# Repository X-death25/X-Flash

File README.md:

# X-Flash
An Open Source CPLD based Sega Megadrive/Genesis Flash Cart 

What is it ?
-----

X-flash is my Sega Megadrive developpement cartridge.
I use it for some research and do all of my hardware test.
It's based on the good old EPM240 and a 64Mb flash memory

Product Feature :
-----

    Rewritable 64 Mb Flash ROM
    192 Macrocells CPLD
    Clean 5V <> 3.3V level shifting
    7 GPIO for user
    Open Source Hardware & Software & PCB

Cartridge supported :
-----
    Classic 32Mb cartridge ( no mapper )

How to use it :
-----

Just flash the needed core into the CPLD and cartridge will works in the same way as an original.
You can reflash memory with any compatible Megadrive reader ( for exemple MD Dumper / Krikkz / Sanni cart Reader )

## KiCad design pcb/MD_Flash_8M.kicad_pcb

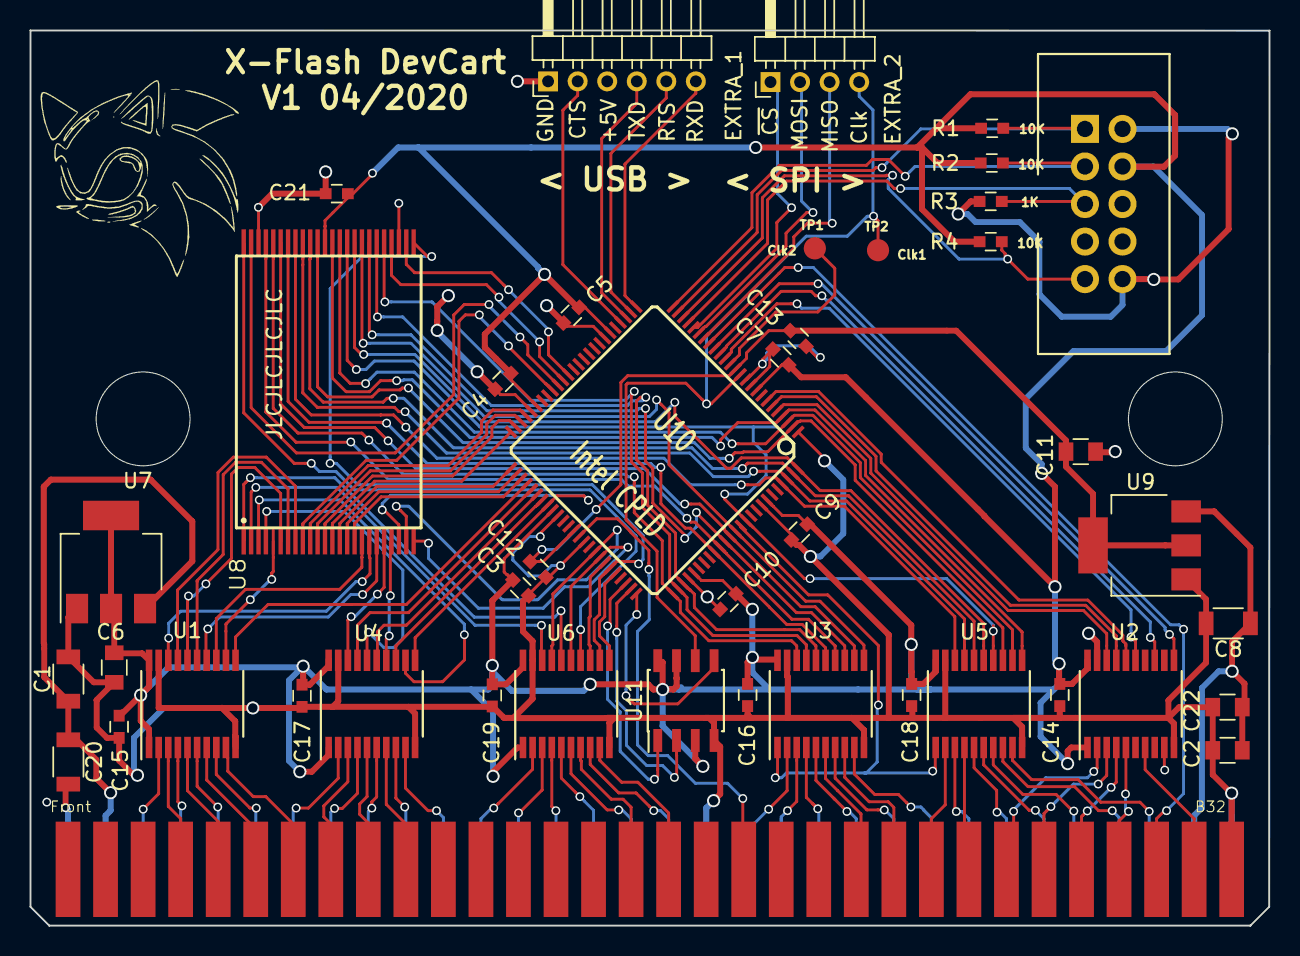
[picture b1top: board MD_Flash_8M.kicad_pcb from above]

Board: 2 copper layers, 83.8 x 60.6 mm, 41 parts (0 on the bottom side), 116 nets.

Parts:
C1, C8, C20: 1206_C; C_1206
C2, C6, C11, C22: C_0805
C3, C4, C5, C7, C9, C10, C12, C13, C14, C15, C16, C17, C18, C19, C21: 0603_CD; C_0603
EXTRA_1: Pin_Header_Angled_1x06_Pitch2.00mm
EXTRA_2: Pin_Header_Angled_1x04_Pitch2.00mm
J1: 0; AVR-JTAG-ICE
MD_Connector1: MD_Connector_H; MEGADRIVE_PCB
R1, R2, R3, R4: R_0603; C_0603
U1, U2, U3, U4, U5, U6: 74LVC245; TSSOP-20_4.4x6.5mm_Pitch0.65mm
U7, U9: SOT-223
U8: MX29LV640; S29GL064
U10: Intel CPLD; TQFP_100
U11: AT25xxx; SOIC-8_3.9x4.9mm_Pitch1.27mm

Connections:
5V1: C2.2, C8.1, C22.2, MD_Connector1.A31, U9.3
5V2: C1.1, C20.1, MD_Connector1.A2, U7.3
A1: MD_Connector1.A17, U6.8
A2: MD_Connector1.A15, U6.5
A3: MD_Connector1.A13, U6.3
A4: MD_Connector1.A11, U4.9
A5: MD_Connector1.A9, U4.6
A6: MD_Connector1.A7, U4.2
A7: MD_Connector1.A5, U1.6
A8: MD_Connector1.A3, U1.2
A9: MD_Connector1.B4, U1.3
A10: MD_Connector1.B5, U1.5
A11: MD_Connector1.A4, U1.4
A12: MD_Connector1.A6, U1.8
A13: MD_Connector1.A8, U4.4
A14: MD_Connector1.A10, U4.8
A15: MD_Connector1.A12, U6.2
A16: MD_Connector1.A14, U6.4
A17: MD_Connector1.A16, U6.6
A18: MD_Connector1.B6, U1.7
A19: MD_Connector1.B7, U1.9
A20: MD_Connector1.B8, U4.3
A21: MD_Connector1.B9, U4.5
A22: MD_Connector1.B10, U4.7
ACC: U8.14, U10.51
BUF_Dir: U3.1, U5.1, U10.89
BYTE: U8.47, U10.41
CE_SPI: U10.73, U11.1
Clk_SPI: EXTRA_2.4, U10.12, U11.6
D0: MD_Connector1.A20, U3.3
D1: MD_Connector1.A23, U3.7
D2: MD_Connector1.A26, U5.5
D3: MD_Connector1.A29, U5.8
D4: MD_Connector1.A28, U5.7
D5: MD_Connector1.A25, U5.3
D6: MD_Connector1.A22, U3.5
D7: MD_Connector1.A19, U3.2
D8: MD_Connector1.A21, U3.4
D9: MD_Connector1.A24, U3.9
D10: MD_Connector1.A27, U5.6
D11: MD_Connector1.A30, U5.9
D12: MD_Connector1.B25, U5.4
D13: MD_Connector1.B24, U5.2
D14: MD_Connector1.B23, U3.8
D15: MD_Connector1.B22, U3.6
FA19: U8.16, U10.53
FA20: U8.9, U10.42
FA21: U8.10, U10.47
FA22: U8.13, U10.50
FCE: U8.26, U10.39
FOE: U8.28, U10.40
GND: C1.2, C2.1, C3.1, C4.2, C5.2, C6.2, C7.2, C8.2, C9.2, C10.2, C11.2, C12.1, C13.1, C14.1, C15.2, C16.1, C17.1, C18.1, C19.1, C20.2, C21.1, C22.1, EXTRA_1.1, J1.2, J1.10, MD_Connector1.A1, MD_Connector1.A18, MD_Connector1.A32, MD_Connector1.B32, R3.2, U1.10, U1.19, U2.10, U3.10, U3.19, U4.10, U4.19, U5.10, U5.19, U6.10, U6.19, U7.1, U8.27, U8.46, U9.1, U10.1, U10.10, U10.11, U10.32, U10.46, U10.60, U10.65, U10.79, U10.93, U11.4
MISO: U10.74, U11.2
MOSI: U10.75, U11.5
RY-BY: U8.15, U10.52
TCK: J1.1, R1.1, U10.24
TDI: J1.9, R4.1, U10.23
TDO: J1.3, R2.1, U10.25
TMS: J1.5, R3.1, U10.22
VA1: U6.12, U8.25, U10.70
VA2: U6.15, U8.24, U10.68
VA3: U6.17, U8.23, U10.67
VA4: U4.11, U8.22, U10.58
VA5: U4.14, U8.21
VA6: U4.18, U8.20
VA7: U1.14, U8.19
VA8: U1.18, U8.18
VA9: U1.17, U8.8
VA10: U1.15, U8.7
VA11: U1.16, U8.6
VA12: U1.12, U8.5
VA13: U4.16, U8.4
VA14: U4.12, U8.3
VA15: U6.18, U8.2
VA16: U6.16, U8.1
VA17: U6.14, U8.48
VA18: U1.13, U8.17
VA19: U1.11, U10.54
VA20: U4.17, U10.55
VA21: U4.15, U10.56
VA22: U4.13, U10.57
VCC2: C11.1, C12.2, C13.2, U9.2, U9.4, U10.13, U10.63
VCC3: C3.2, C4.1, C5.1, C6.1, C7.1, C9.1, C10.1, C14.2, C15.1, C16.2, C17.2, C18.2, C19.2, C21.2, J1.4, R1.2, R2.2, R4.2, U1.1, U1.20, U2.1, U2.20, U3.20, U4.1, U4.20, U5.20, U6.1, U6.20, U7.2, U7.4, U8.37, U10.9, U10.31, U10.45, U10.59, U10.80, U10.94, U11.3, U11.7, U11.8
VD0: U3.17, U8.29, U10.77
VD1: U3.13, U8.31, U10.86
VD2: U5.15, U8.33, U10.100
VD3: U5.12, U8.35, U10.3
VD4: U5.13, U8.38, U10.2
VD5: U5.17, U8.40, U10.98
VD6: U3.15, U8.42, U10.84
VD7: U3.18, U8.44, U10.76
VD8: U3.16, U8.30, U10.78
VD9: U3.11, U8.32, U10.88
VD10: U5.14, U8.34, U10.90
VD11: U5.11, U8.36, U10.4
VD12: U5.16, U8.39, U10.99
VD13: U5.18, U8.41, U10.97
VD14: U3.12, U8.43, U10.87
VD15: U3.14, U8.45, U10.85
WE: U8.11, U10.48
~ASEL: MD_Connector1.B26, U2.2
~CE_ROM: MD_Connector1.B17, U6.9
~Mark3: MD_Connector1.B30, U10.18
~OE_ROM: MD_Connector1.B16, U6.7
~Soft_Rst: MD_Connector1.B27, U2.3
~TIME: MD_Connector1.B31, U2.7
~UWR: MD_Connector1.B29, U2.5
~V68K_Rst: U2.11, U10.17
~VASEL: U2.18, U10.5
~VCE: U6.11, U10.71
~VOE: U6.13, U10.69
~VRst: U2.17, U10.6
~VTIME: U2.13, U10.16
~VUWR: U2.15, U10.15
~VWE: U2.16, U10.7
~WE_ROM: MD_Connector1.B28, U2.4

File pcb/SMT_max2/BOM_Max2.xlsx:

Comment | Designator | Footprint | LCSC Part
Level Shifter | U1,U2,U3,U4,U5,U6 | 74LVC245 | C6082
Flash 64Mb | U8 | MX29LV640 | C30076
Regulateur 3,3V | U7,U9 | AMS1117 3,3V | C6186
MAX2 CPLD | U10 | EPM240T100C5N | C10041
100nF SMD 0603 | C3 ,C4,C5,C7,C9,C10,C12,C13,C14,C15,C16,C17,C18,C19,C21 | 0603_CD | C14663
10µF SMD 1206 | C1,C8 | 0603_CR | C13585
22µF SMD 0805 | C6,C11,C2,C22 | 0603_CR | C45783
100nF SMD 1206 | C20 | 1206_C | C24497
10K SMD 0603 | R1,R2,R4 | R_0603 | C25804
1K SMD 0603 | R3 | R_0603 | C21190

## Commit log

2020-12-04 Add some works
